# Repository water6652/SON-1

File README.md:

# MacroPad SON-1
MacroPad SON-1 is a simple seeeduino xiao macropad built for the "HackPad" HackClub project that features:

**1. 2x4 Key matrix**: 2 colums, 4 rows, utilises only 6 pins on the microcontroller.

**2. Rotary encoder with switch**: perfect for audio adjustments or muting audio entirely.

**3. 0.91-inch OLED display**: a resloution of 128x32 pixels, enough to play doom or bad apple.

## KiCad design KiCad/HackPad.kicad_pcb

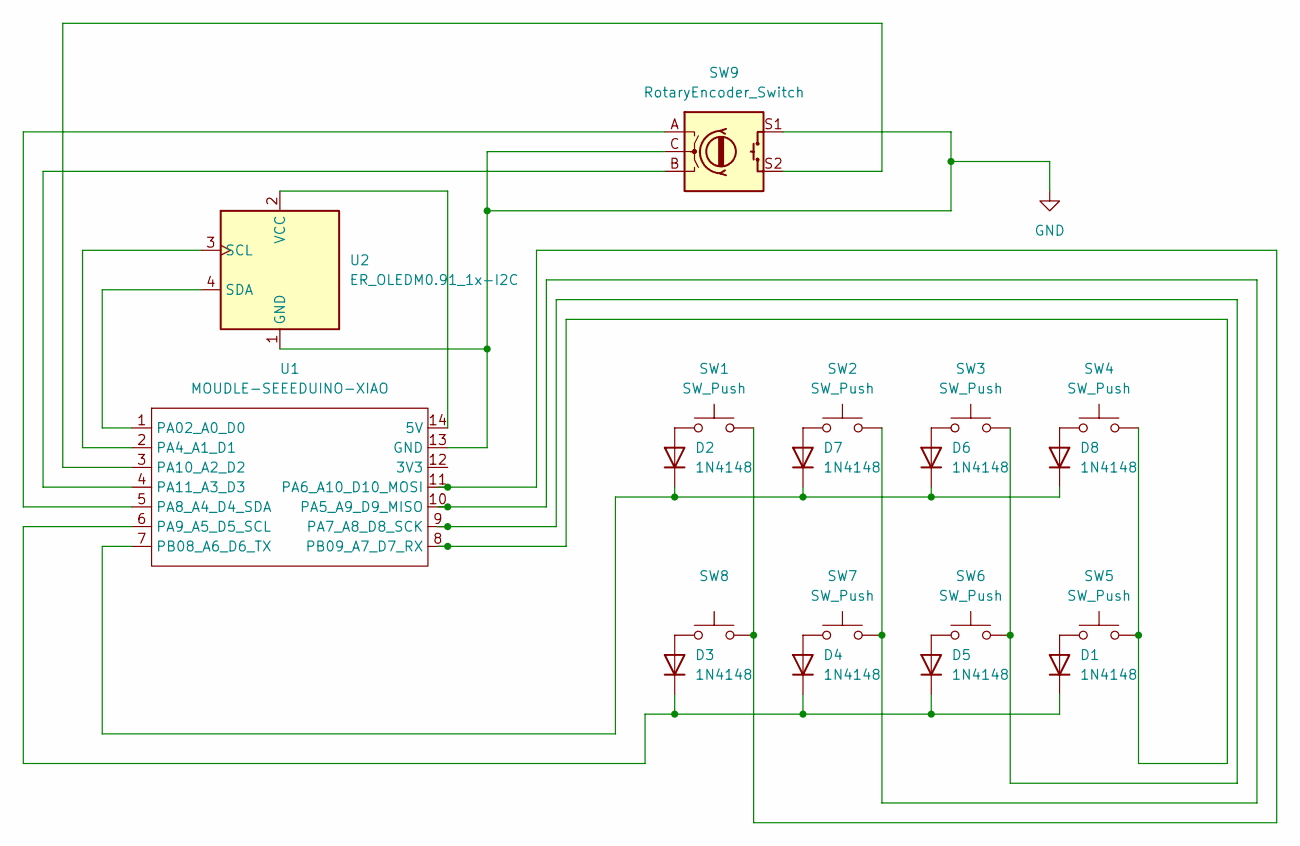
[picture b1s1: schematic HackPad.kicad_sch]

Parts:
D1, D2, D3, D4, D5, D6, D7, D8: 1N4148; D_DO-35_SOD27_P7.62mm_Horizontal
SW1, SW2, SW3, SW4, SW5, SW6, SW7, SW8: SW_Push; SW_Cherry_MX_1.00u_PCB
SW9: RotaryEncoder_Switch; RotaryEncoder_Alps_EC11E-Switch_Vertical_H20mm
U1: MOUDLE-SEEEDUINO-XIAO; XIAO-Generic-Hybrid-14P-2.54-21X17.8MM
U2: ER_OLEDM0.91_1x-I2C

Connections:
GND: SW9.C, SW9.S1, U1.13 (GND), U2.1 (GND)
unnamed: D1.2 (A), SW5.1
unnamed: D1.1 (K), D3.1 (K), D4.1 (K), D5.1 (K), U1.6 (PA9_A5_D5_SCL)
unnamed: D2.2 (A), SW1.1
unnamed: D2.1 (K), D6.1 (K), D7.1 (K), D8.1 (K), U1.7 (PB08_A6_D6_TX)
unnamed: D3.2 (A), SW8.1
unnamed: D4.2 (A), SW7.1
unnamed: D5.2 (A), SW6.1
unnamed: D6.2 (A), SW3.1
unnamed: D7.2 (A), SW2.1
unnamed: D8.2 (A), SW4.1
unnamed: U1.14 (5V), U2.2 (VCC)
unnamed: U1.1 (PA02_A0_D0), U2.4 (SDA)
unnamed: U1.2 (PA4_A1_D1), U2.3 (SCL)
unnamed: SW2.2, SW7.2, U1.10 (PA5_A9_D9_MISO)
unnamed: SW1.2, SW8.2, U1.11 (PA6_A10_D10_MOSI)
unnamed: SW3.2, SW6.2, U1.9 (PA7_A8_D8_SCK)
unnamed: SW9.A, U1.5 (PA8_A4_D4_SDA)
unnamed: SW9.S2, U1.3 (PA10_A2_D2)
unnamed: SW9.B, U1.4 (PA11_A3_D3)
unnamed: SW4.2, SW5.2, U1.8 (PB09_A7_D7_RX)

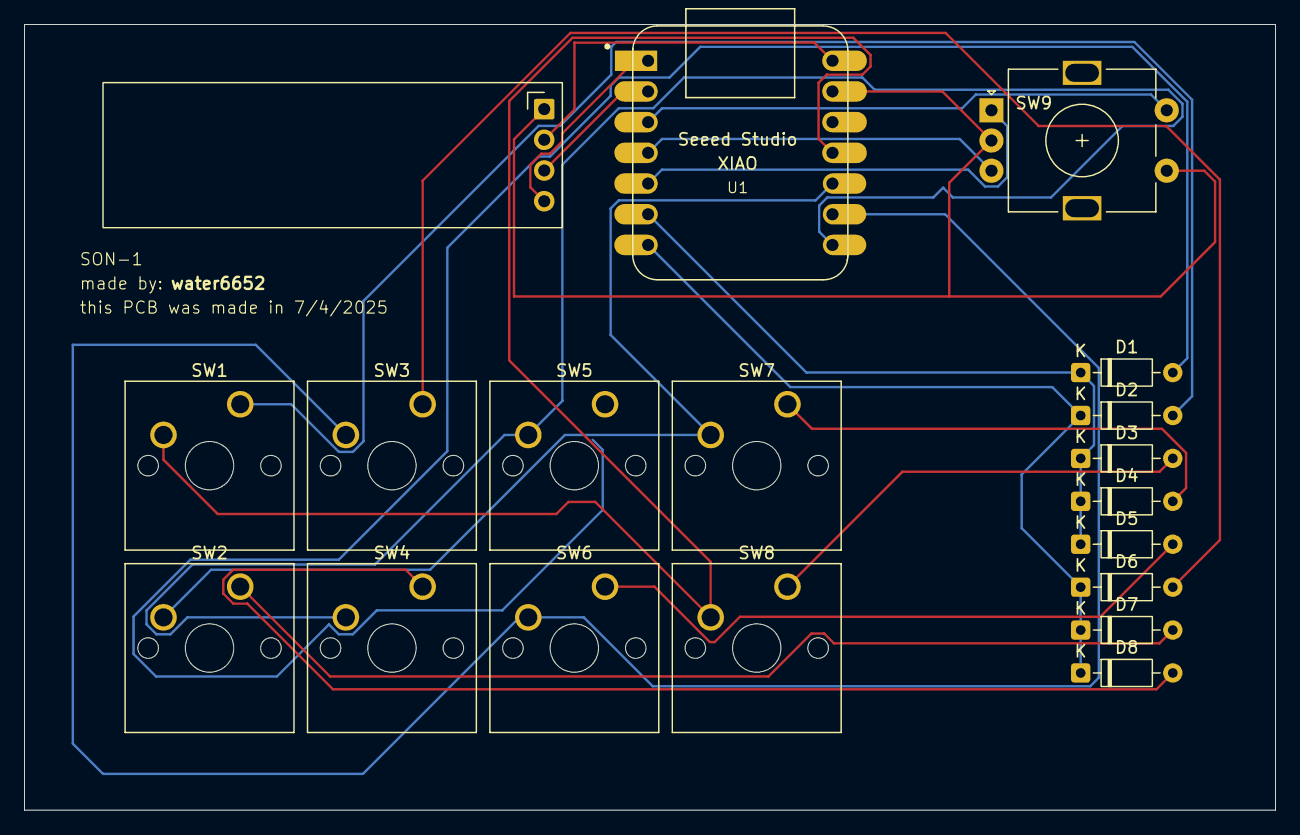
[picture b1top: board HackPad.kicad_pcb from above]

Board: 2 copper layers, 103.5 x 65.0 mm, 19 parts (0 on the bottom side), 21 nets.
